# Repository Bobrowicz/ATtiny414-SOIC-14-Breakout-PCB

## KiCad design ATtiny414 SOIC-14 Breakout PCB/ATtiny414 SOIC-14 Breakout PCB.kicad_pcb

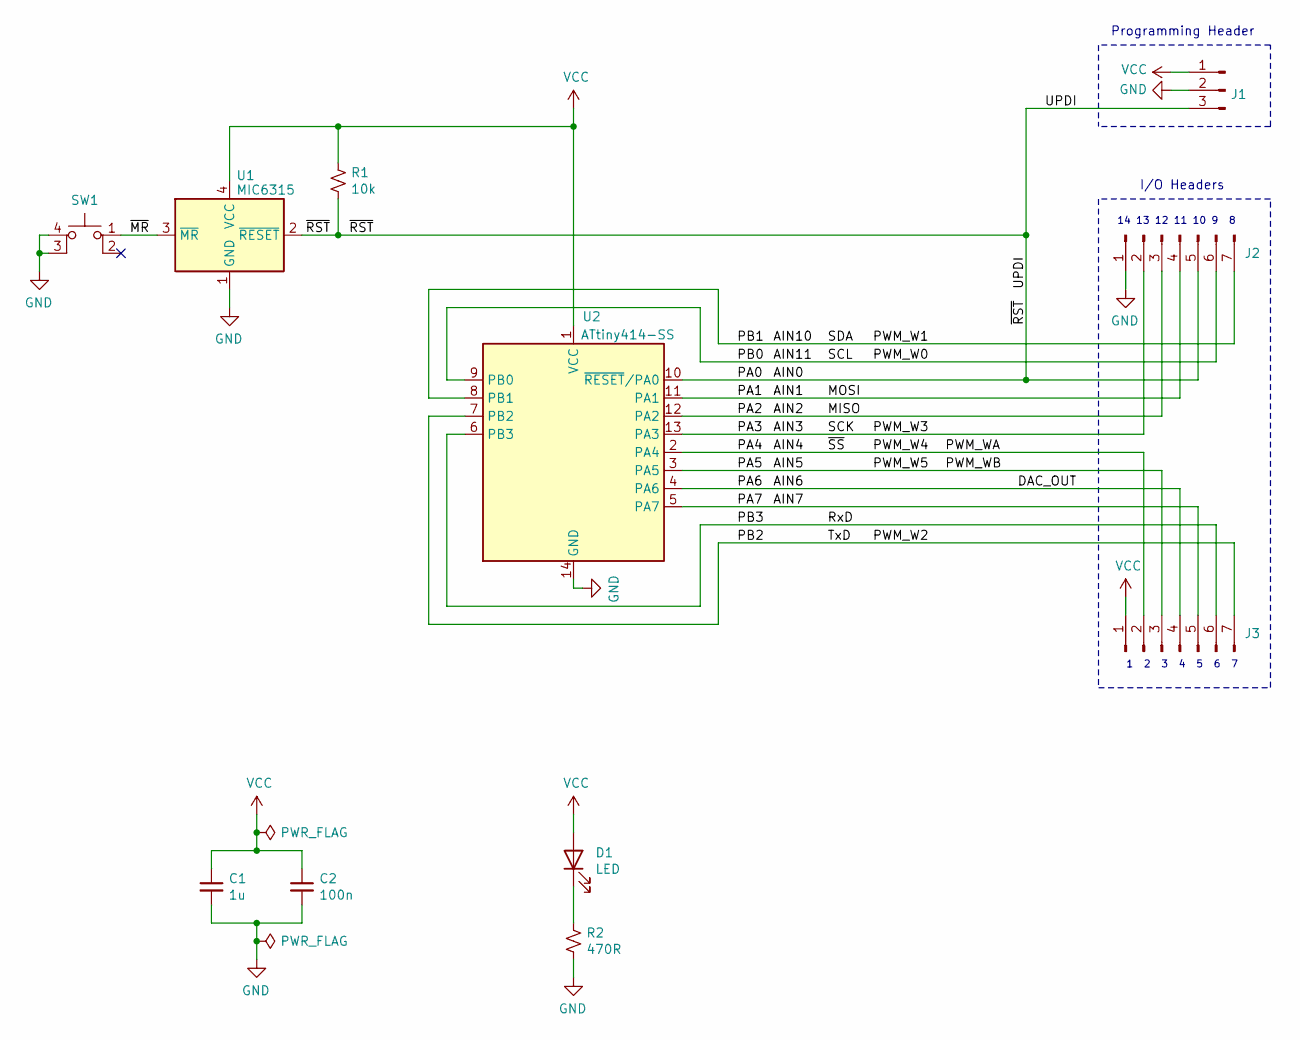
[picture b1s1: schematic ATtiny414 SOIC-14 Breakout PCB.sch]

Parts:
C1: 1u; C_0805_HandSoldering
C2: 100n; C_0805_HandSoldering
D1: LED; LED_0805_HandSoldering
J1: Conn_01x03_Male; Pin_Header_Straight_1x03_Pitch2.54mm
J2, J3: Conn_01x07_Male; Pin_Header_Straight_1x07_Pitch2.54mm
R1: 10k; R_0805_HandSoldering
R2: 470R; R_0805_HandSoldering
SW1: SW_MEC_5E; TL3305AF160QG
U1: MIC6315; SOT-143
U2: ATtiny414-SS; SOIC-14_N

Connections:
/AIN0: J1.3, J2.5, R1.2, U1.2 (~RESET), U2.10 (~RESET~/PA0)
/AIN1: J2.4, U2.11 (PA1)
/AIN2: J2.3, U2.12 (PA2)
/AIN3: J2.2, U2.13 (PA3)
/AIN4: J3.2, U2.2 (PA4)
/AIN5: J3.3, U2.3 (PA5)
/AIN6: J3.4, U2.4 (PA6)
/AIN7: J3.5, U2.5 (PA7)
/AIN10: J2.7, U2.8 (PB1)
/AIN11: J2.6, U2.9 (PB0)
/PB2: J3.7, U2.7 (PB2)
/PB3: J3.6, U2.6 (PB3)
/~MR: SW1.1, U1.3 (~MR)
GND: C1.2, C2.2, J1.2, J2.1, R2.2, SW1.3 (K), SW1.4 (A), U1.1 (GND), U2.14 (GND)
unnamed: D1.1 (K), R2.1
VCC: C1.1, C2.1, D1.2 (A), J1.1, J3.1, R1.1, U1.4 (VCC), U2.1 (VCC)

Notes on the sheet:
1 2 3 4 5 6 7
I/O Headers
Programming Header
14 13 12 11 10 9 8

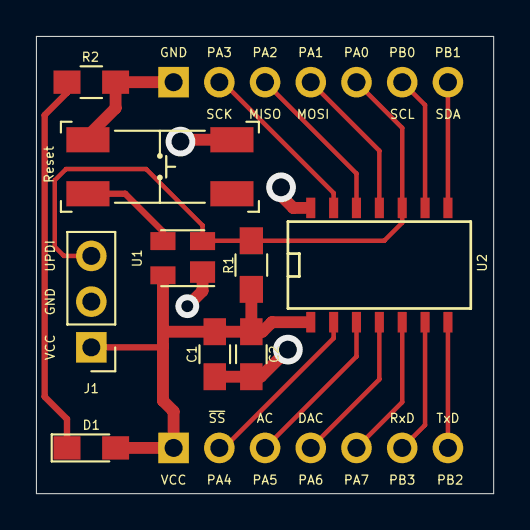
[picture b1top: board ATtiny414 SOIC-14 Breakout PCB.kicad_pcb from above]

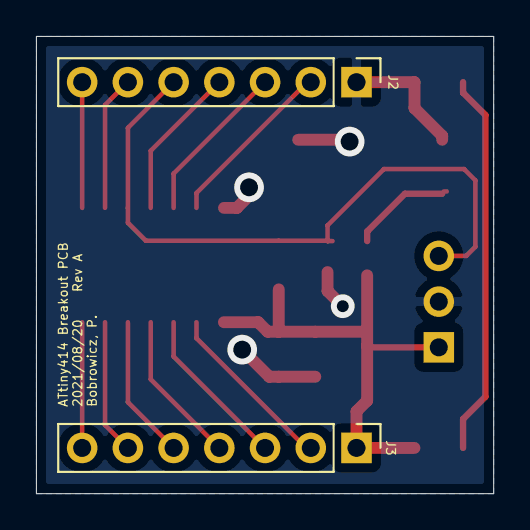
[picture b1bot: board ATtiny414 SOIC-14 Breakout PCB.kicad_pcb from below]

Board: 2 copper layers, 25.4 x 25.4 mm, 11 parts (2 on the bottom side), 16 nets.
